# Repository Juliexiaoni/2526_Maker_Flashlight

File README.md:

# 2526_Maker_Flashlight
Objectif : Concevoir une lampe d'éclairage sur un vélo afin d'augmenter la sécutité en étant plus visible. 

### Cahier des charges : 
- 3 modes d’éclairages
- Étanche
- Bonus pour le rendre avancée : énergie solaire, allumage automatique (capteur luminosité)

### Planning prévisionnel : 
1. Etablir une analyse fonctionnelle et la BOM
2. Schématique et routage conception électronique
3. CAO pour le boitier
4. Assemblage et test

Le boîtier consiste à réaliser un suppport qui se clipse sur une attache en caoutchouc. 

La distance laissée entre les composants de la couche arrière et le support permet d’utiliser le bouton pour allumer et éteindre la lumière.

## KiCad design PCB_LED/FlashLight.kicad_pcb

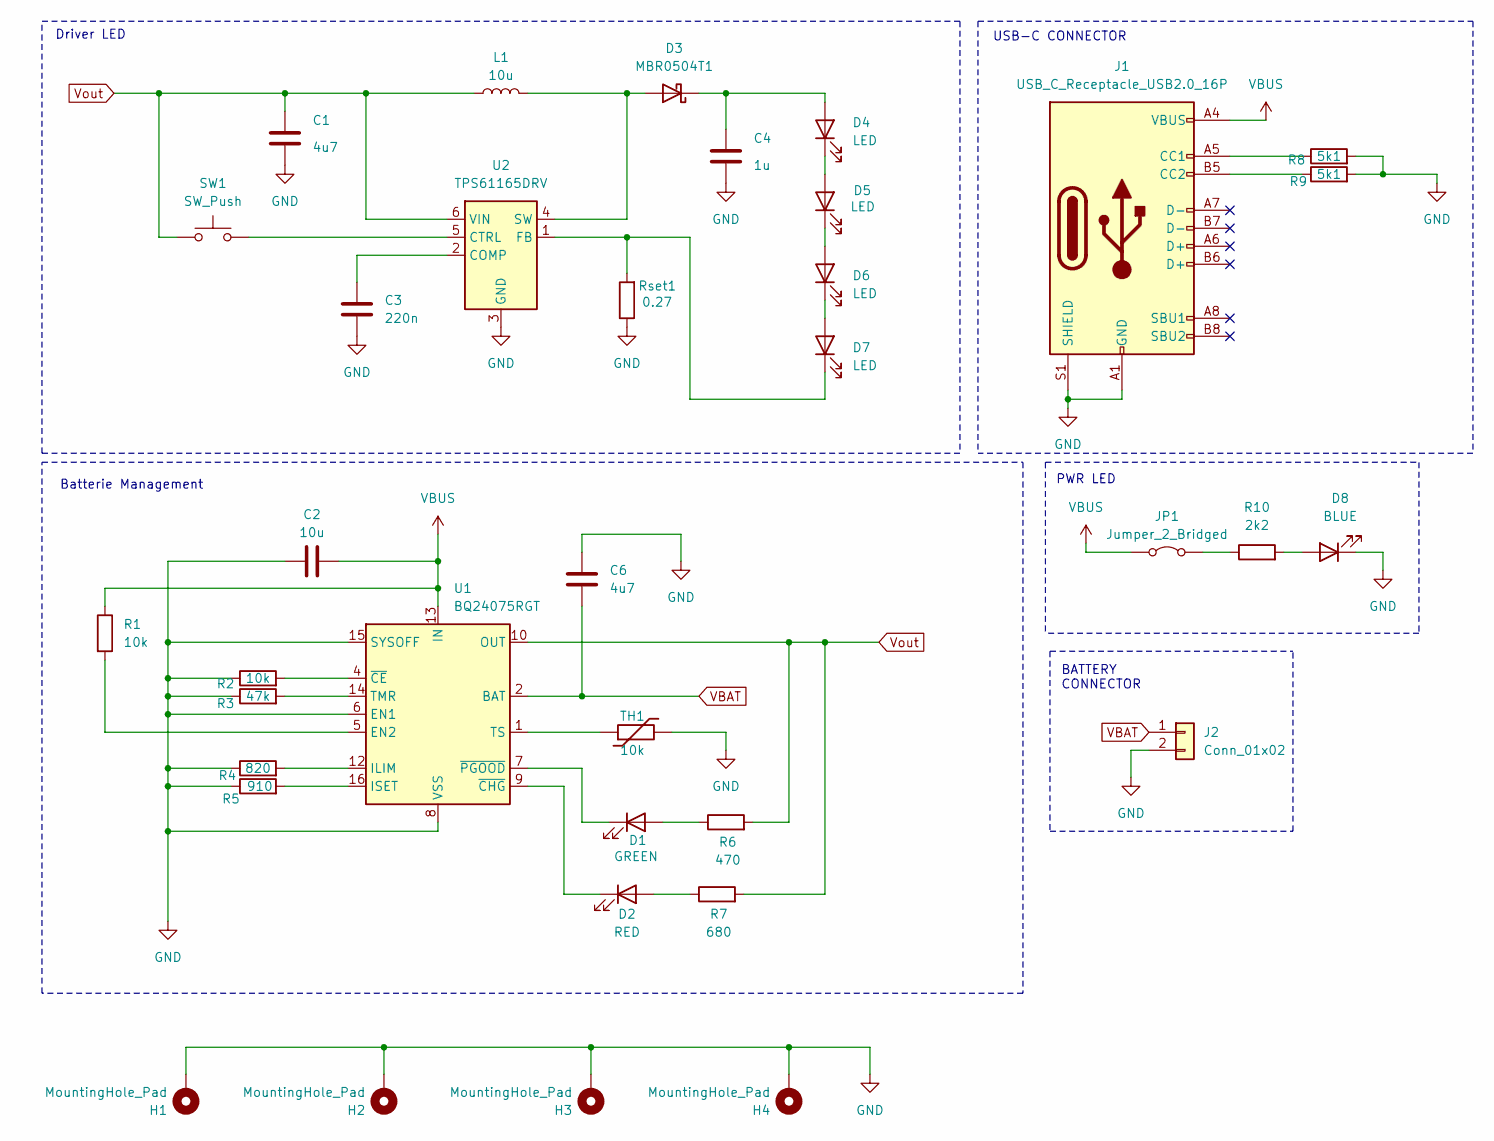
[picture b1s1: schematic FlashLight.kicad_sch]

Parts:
C1, C6: 4u7; C_0603_1608Metric_Pad1.08x0.95mm_HandSolder
C2: 10u; C_0603_1608Metric_Pad1.08x0.95mm_HandSolder
C3: 220n; C_0603_1608Metric_Pad1.08x0.95mm_HandSolder
C4: 1u; C_0603_1608Metric_Pad1.08x0.95mm_HandSolder
D1: GREEN; D_0603_1608Metric_Pad1.05x0.95mm_HandSolder
D2: RED; D_0603_1608Metric_Pad1.05x0.95mm_HandSolder
D3: MBR0504T1; D_SOD-123
D4, D5, D6, D7: LED; LED_Cree-XP
D8: BLUE; LED_0603_1608Metric_Pad1.05x0.95mm_HandSolder
H1, H2, H3, H4: MountingHole_Pad; MountingHole_2.2mm_M2_DIN965_Pad
J1: USB_C_Receptacle_USB2.0_16P; USB_C_Receptacle_GCT_USB4105-xx-A_16P_TopMnt_Horizontal
J2: Conn_01x02; JST_PH_B2B-PH-K_1x02_P2.00mm_Vertical
JP1: Jumper_2_Bridged; SolderJumper-2_P1.3mm_Open_Pad1.0x1.5mm
L1: 10u; L_Wuerth_WE-PD-Typ-7345
R1, R2: 10k; R_0402_1005Metric_Pad0.72x0.64mm_HandSolder
R3: 47k; R_0402_1005Metric_Pad0.72x0.64mm_HandSolder
R4: 820; R_0402_1005Metric_Pad0.72x0.64mm_HandSolder
R5: 910; R_0402_1005Metric_Pad0.72x0.64mm_HandSolder
R6: 470; R_0402_1005Metric_Pad0.72x0.64mm_HandSolder
R7: 680; R_0402_1005Metric_Pad0.72x0.64mm_HandSolder
R8, R9: 5k1; R_0402_1005Metric_Pad0.72x0.64mm_HandSolder
R10: 2k2; R_0402_1005Metric_Pad0.72x0.64mm_HandSolder
Rset1: 0.27; R_0402_1005Metric_Pad0.72x0.64mm_HandSolder
SW1: SW_Push; SW_PUSH_6mm
TH1: 10k; R_0603_1608Metric_Pad0.98x0.95mm_HandSolder
U1: BQ24075RGT; VQFN-16-1EP_3x3mm_P0.5mm_EP1.6x1.6mm
U2: TPS61165DRV; WSON-6-1EP_2x2mm_P0.65mm_EP1x1.6mm

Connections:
GND: C1.2, C2.1, C3.2, C4.2, C6.1, D8.1 (K), H1.1, H2.1, H3.1, H4.1, J1.A1 (GND), J1.A12 (GND), J1.B1 (GND), J1.B12 (GND), J1.S1 (SHIELD), J2.2, R2.1, R3.1, R4.1, R5.1, R8.2, R9.2, Rset1.1, TH1.2, U1.6 (EN1), U1.8 (VSS), U1.15 (SYSOFF), U1.17 (VSS), U2.3 (GND), U2.7 (GND)
unnamed: D1.2 (A), R6.1
unnamed: D1.1 (K), U1.7 (~PGOOD)
unnamed: D2.2 (A), R7.1
unnamed: D2.1 (K), U1.9 (~CHG)
unnamed: D3.2 (A), L1.2, U2.4 (SW)
unnamed: C4.1, D3.1 (K), D4.2 (A)
unnamed: D4.1 (K), D5.2 (A)
unnamed: D5.1 (K), D6.2 (A)
unnamed: D6.1 (K), D7.2 (A)
unnamed: D7.1 (K), Rset1.2, U2.1 (FB)
unnamed: D8.2 (A), R10.2
unnamed: J1.A5 (CC1), R8.1
unnamed: J1.B5 (CC2), R9.1
unnamed: JP1.2 (B), R10.1
unnamed: R1.2, U1.5 (EN2)
unnamed: R4.2, U1.12 (ILIM)
unnamed: R5.2, U1.16 (ISET)
unnamed: R3.2, U1.14 (TMR)
unnamed: TH1.1, U1.1 (TS)
unnamed: R2.2, U1.4 (~CE)
unnamed: C3.1, U2.2 (COMP)
unnamed: SW1.2, U2.5 (CTRL)
VBAT: C6.2, J2.1, U1.2 (BAT), U1.3 (BAT)
VBUS: C2.2, J1.A4 (VBUS), J1.A9 (VBUS), J1.B4 (VBUS), J1.B9 (VBUS), JP1.1 (A), R1.1, U1.13 (IN)
Vout: C1.1, L1.1, R6.2, R7.2, SW1.1, U1.10 (OUT), U1.11 (OUT), U2.6 (VIN)

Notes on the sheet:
Driver LED
Batterie Management
BATTERY CONNECTOR
PWR LED
USB-C CONNECTOR

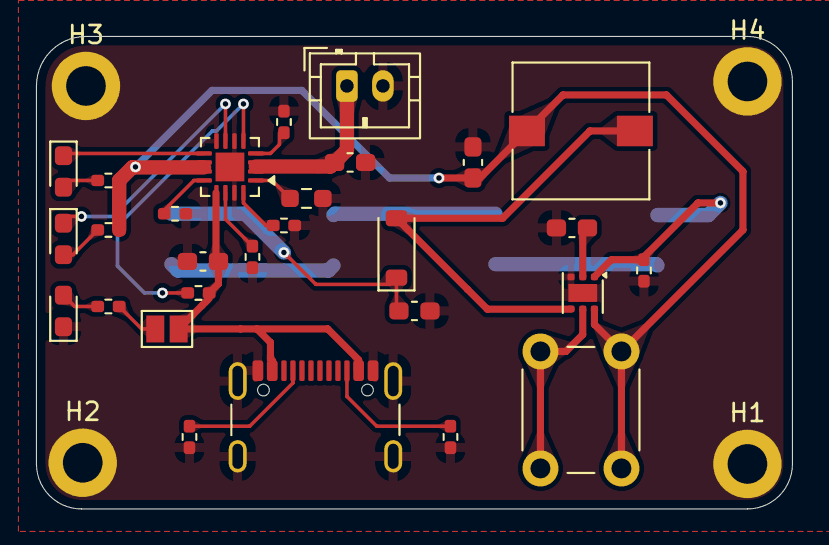
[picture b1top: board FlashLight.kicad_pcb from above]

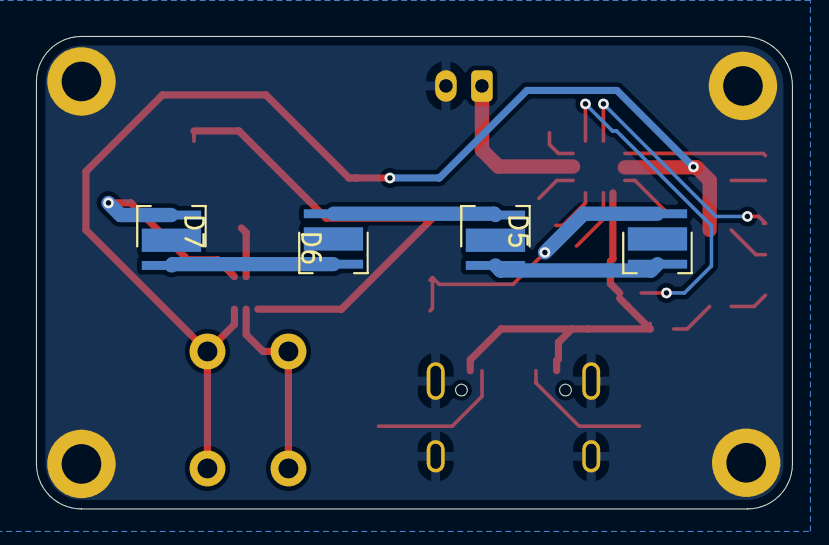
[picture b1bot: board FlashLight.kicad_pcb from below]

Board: 2 copper layers, 42.0 x 26.2 mm, 36 parts (4 on the bottom side), 26 nets.

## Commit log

2026-01-19 Update README with project specifications and planning
    Added project requirements and planning details.
2026-01-23 Update project objective in README
    Clarified project objective in README.
2026-01-23 Update project objective and description in README
2026-03-26 Schématique_LED
2026-03-30 Update project objective for visibility and safety
2026-03-30 Driver TI
2026-03-30 Modif 1
2026-04-02 Layout
2026-05-06 3D impression
2026-05-06 Update images in README.md for better clarity
